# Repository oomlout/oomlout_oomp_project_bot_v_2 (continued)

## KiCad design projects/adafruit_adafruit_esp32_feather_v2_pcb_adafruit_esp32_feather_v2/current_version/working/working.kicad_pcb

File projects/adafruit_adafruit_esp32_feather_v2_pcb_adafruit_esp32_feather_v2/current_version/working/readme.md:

# adafruit_esp32_feather_v2_pcb
 
## summary 
* id: adafruit_adafruit_esp32_feather_v2_pcb_adafruit_esp32_feather_v2
* user: adafruit
* name: adafruit_esp32_feather_v2_pcb
* board: adafruit_esp32_feather_v2
* repo: https://github.com/adafruit/Adafruit-ESP32-Feather-V2-PCB

* src_file_repo_sch: 
* src_file_repo_sch_link: https://github.com/adafruit/Adafruit-ESP32-Feather-V2-PCB/tree/main/
* full details link: https://github.com/oomlout/oomlout_oomp_project_bot_v_2/tree/main/projects/adafruit_adafruit_esp32_feather_v2_pcb_adafruit_esp32_feather_v2/current_version/working  

## schematic  
  
[schematic (pdf)](working_schematic.pdf) 

## pcb  

[board (pdf)](working.pdf)  

## working_bom
| Id | Designator | Footprint | Quantity | Designation | Supplier and ref |  | None | 
| --- | --- | --- | --- | --- | --- | --- | --- | 
| 1 | LED1 | LED3535 | 1 | WS2812B3535 |  |  | [''] | 
| 2 | R9 | RESPACK_4X0603 | 1 | 47K |  |  | [''] | 
| 3 | D4 | SOD-123 | 1 | MBR540 |  |  | [''] | 
| 4 | R3,R1 | 0603-NO | 2 | 200K |  |  | [''] | 
| 5 | R4,R2,R5,R6,R10 | 0603-NO | 5 | 5.1K |  |  | [''] | 
| 6 | U$34,U$35 | FIDUCIAL_1MM | 2 | FIDUCIAL_1MM |  |  | [''] | 
| 7 | C1,C2,C13 | 0805-NO | 3 | 10uF |  |  | [''] | 
| 8 | JP1 | 1X16_ROUND | 1 |  |  |  | [''] | 
| 9 | U$31,U$32 | MOUNTINGHOLE_2.5_PLATED | 2 | MOUNTINGHOLE2.5 |  |  | [''] | 
| 10 | CHG0 | CHIPLED_0603_NOOUTLINE | 1 | ORANGE |  |  | [''] | 
| 11 | U2,U1 | SOT23-5 | 2 | AP2112-3.3 |  |  | [''] | 
| 12 | C8,C3,C7,C6 | 0805-NO | 4 | 10ÂµF |  |  | [''] | 
| 13 | C5,C4,C9,C10 | 0603-NO | 4 | 1uF |  |  | [''] | 
| 14 | Q5 | SOT363 | 1 | DUAL NPN |  |  | [''] | 
| 15 | @HOLE0,@HOLE1 |  | 2 |  |  |  | [''] | 
| 16 | U$14 | ADAFRUIT_2.5MM | 1 |  |  |  | [''] | 
| 17 | JP3 | 1X12_ROUND | 1 |  |  |  | [''] | 
| 18 | D3 | CHIPLED_0603_NOOUTLINE | 1 | RED |  |  | [''] | 
| 19 | U$15 | ADAFRUIT_3.5MM | 1 |  |  |  | [''] | 
| 20 | R7,R12 | 0603-NO | 2 | 100K |  |  | [''] | 
| 21 | CONN1 | JST_SH4_RA | 1 | STEMMA_I2C_QTRA |  |  | [''] | 
| 22 | X6 | USB_C_CUSB31-CFM2AX-01-X | 1 | USB Type C |  |  | [''] | 
| 23 | SW1,SW2 | BTN_KMR2_4.6X2.8 | 2 | KMR2 |  |  | [''] | 
| 24 | IC3 | QFN24_4MM_SMSC | 1 | CP2102N-24 |  |  | [''] | 
| 25 | Q3 | SOT23-R | 1 | DMG3415U |  |  | [''] | 
| 26 | R13 | RESPACK_4X0603 | 1 | 10K |  |  | [''] | 
| 27 | C12,C11 | 0603-NO | 2 | 0.1uF |  |  | [''] | 
| 28 | X3 | ESP32-PICO-MINI | 1 | ESP32-PICO-MINI-02MINI |  |  | [''] | 
| 29 | U3 | SOT23-5 | 1 | MCP73831T-2ACI/OT |  |  | [''] | 
| 30 | X1 | JSTPH2_BATT | 1 | JSTPH |  |  | [''] | 
| 31 | D+1,D-1 | B1,27 | 2 | TPB1,27 |  |  | [''] | 
| 32 | U$43 | HUZZAH32 | 1 |  |  |  | [''] | 
| 33 | U$7 | ADAFRUIT_5MM | 1 |  |  |  | [''] | 
| 34 | U$13 | PCBFEAT-REV-040 | 1 |  |  |  | [''] | 
| 35 | U$9 | FEATHERLOGO_MED | 1 |  |  |  | [''] | 

## bom_schematic
| Ref | Qnty | Value | Cmp name | Footprint | Description | Vendor | DNP | 
| --- | --- | --- | --- | --- | --- | --- | --- | 
| C1, C2, C13 | 3 | 10uF | CAP_CERAMIC0805-NOOUTLINE | working:0805-NO |  |  |  | 
| C3, C6, C7, C8 | 4 | 10ÂµF | CAP_CERAMIC0805-NOOUTLINE | working:0805-NO |  |  |  | 
| C4, C5, C9, C10 | 4 | 1uF | CAP_CERAMIC0603_NO | working:0603-NO |  |  |  | 
| C11, C12 | 2 | 0.1uF | CAP_CERAMIC0603_NO | working:0603-NO |  |  |  | 
| CHG0 | 1 | ORANGE | LED0603_NOOUTLINE | working:CHIPLED_0603_NOOUTLINE |  |  |  | 
| CONN1 | 1 | STEMMA_I2C_QTRA | STEMMA_I2C_QTRA | working:JST_SH4_RA |  |  |  | 
| D3 | 1 | RED | LED0603_NOOUTLINE | working:CHIPLED_0603_NOOUTLINE |  |  |  | 
| D4 | 1 | MBR540 | DIODE-SCHOTTKYSOD-123 | working:SOD-123 |  |  |  | 
| D+1 | 1 | TPB1,27 | TPB1,27 | working:B1,27 |  |  |  | 
| D-1 | 1 | TPB1,27 | TPB1,27 | working:B1,27 |  |  |  | 
| IC3 | 1 | CP2102N-24 | CP2102N-24 | working:QFN24_4MM_SMSC |  |  |  | 
| JP1 | 1 | HEADER-1X16ROUND | HEADER-1X16ROUND | working:1X16_ROUND |  |  |  | 
| JP3 | 1 | HEADER-1X12 | HEADER-1X12 | working:1X12_ROUND |  |  |  | 
| LED1 | 1 | WS2812B3535 | WS2812B3535 | working:LED3535 |  |  |  | 
| Q3 | 1 | DMG3415U | MOSFET-P | working:SOT23-R |  |  |  | 
| Q5 | 1 | DUAL NPN | MOSFET-N_DUAL | working:SOT363 |  |  |  | 
| R1, R3 | 2 | 200K | RESISTOR_0603_NOOUT | working:0603-NO |  |  |  | 
| R2, R4, R5, R6, R10 | 5 | 5.1K | RESISTOR_0603_NOOUT | working:0603-NO |  |  |  | 
| R7, R12 | 2 | 100K | RESISTOR_0603_NOOUT | working:0603-NO |  |  |  | 
| R9 | 1 | 47K | RESISTOR_4PACK | working:RESPACK_4X0603 |  |  |  | 
| R13 | 1 | 10K | RESISTOR_4PACK | working:RESPACK_4X0603 |  |  |  | 
| SW1, SW2 | 2 | KMR2 | SWITCH_TACT_SMT4.6X2.8 | working:BTN_KMR2_4.6X2.8 |  |  |  | 
| U1, U2 | 2 | AP2112-3.3 | VREG_SOT23-5 | working:SOT23-5 |  |  |  | 
| U3 | 1 | MCP73831T-2ACI/OT | MCP73831/2 | working:SOT23-5 |  |  |  | 
| U$31, U$32 | 2 | MOUNTINGHOLE2.5 | MOUNTINGHOLE2.5 | working:MOUNTINGHOLE_2.5_PLATED |  |  |  | 
| U$34, U$35 | 2 | FIDUCIAL_1MM | FIDUCIAL_1MM | working:FIDUCIAL_1MM |  |  |  | 
| X1 | 1 | CON_JST_PH_2PIN_MT_BATT | CON_JST_PH_2PIN_MT_BATT | working:JSTPH2_BATT |  |  |  | 
| X3 | 1 | ESP32-PICO-MINI-02MINI | ESP32-PICO-MINI-02MINI | working:ESP32-PICO-MINI |  |  |  | 
| X6 | 1 | USB Type C | USB_C | working:USB_C_CUSB31-CFM2AX-01-X |  |  |  | 

## mounting_holes
| x | y | package | value | ref | size | 
| --- | --- | --- | --- | --- | --- | 
| 0.0 | 17.78 | MOUNTINGHOLE_2.5_PLATED | MOUNTINGHOLE2.5 | U$31 | m3 | 
| 0.0 | 0.0 | MOUNTINGHOLE_2.5_PLATED | MOUNTINGHOLE2.5 | U$32 | m3 |

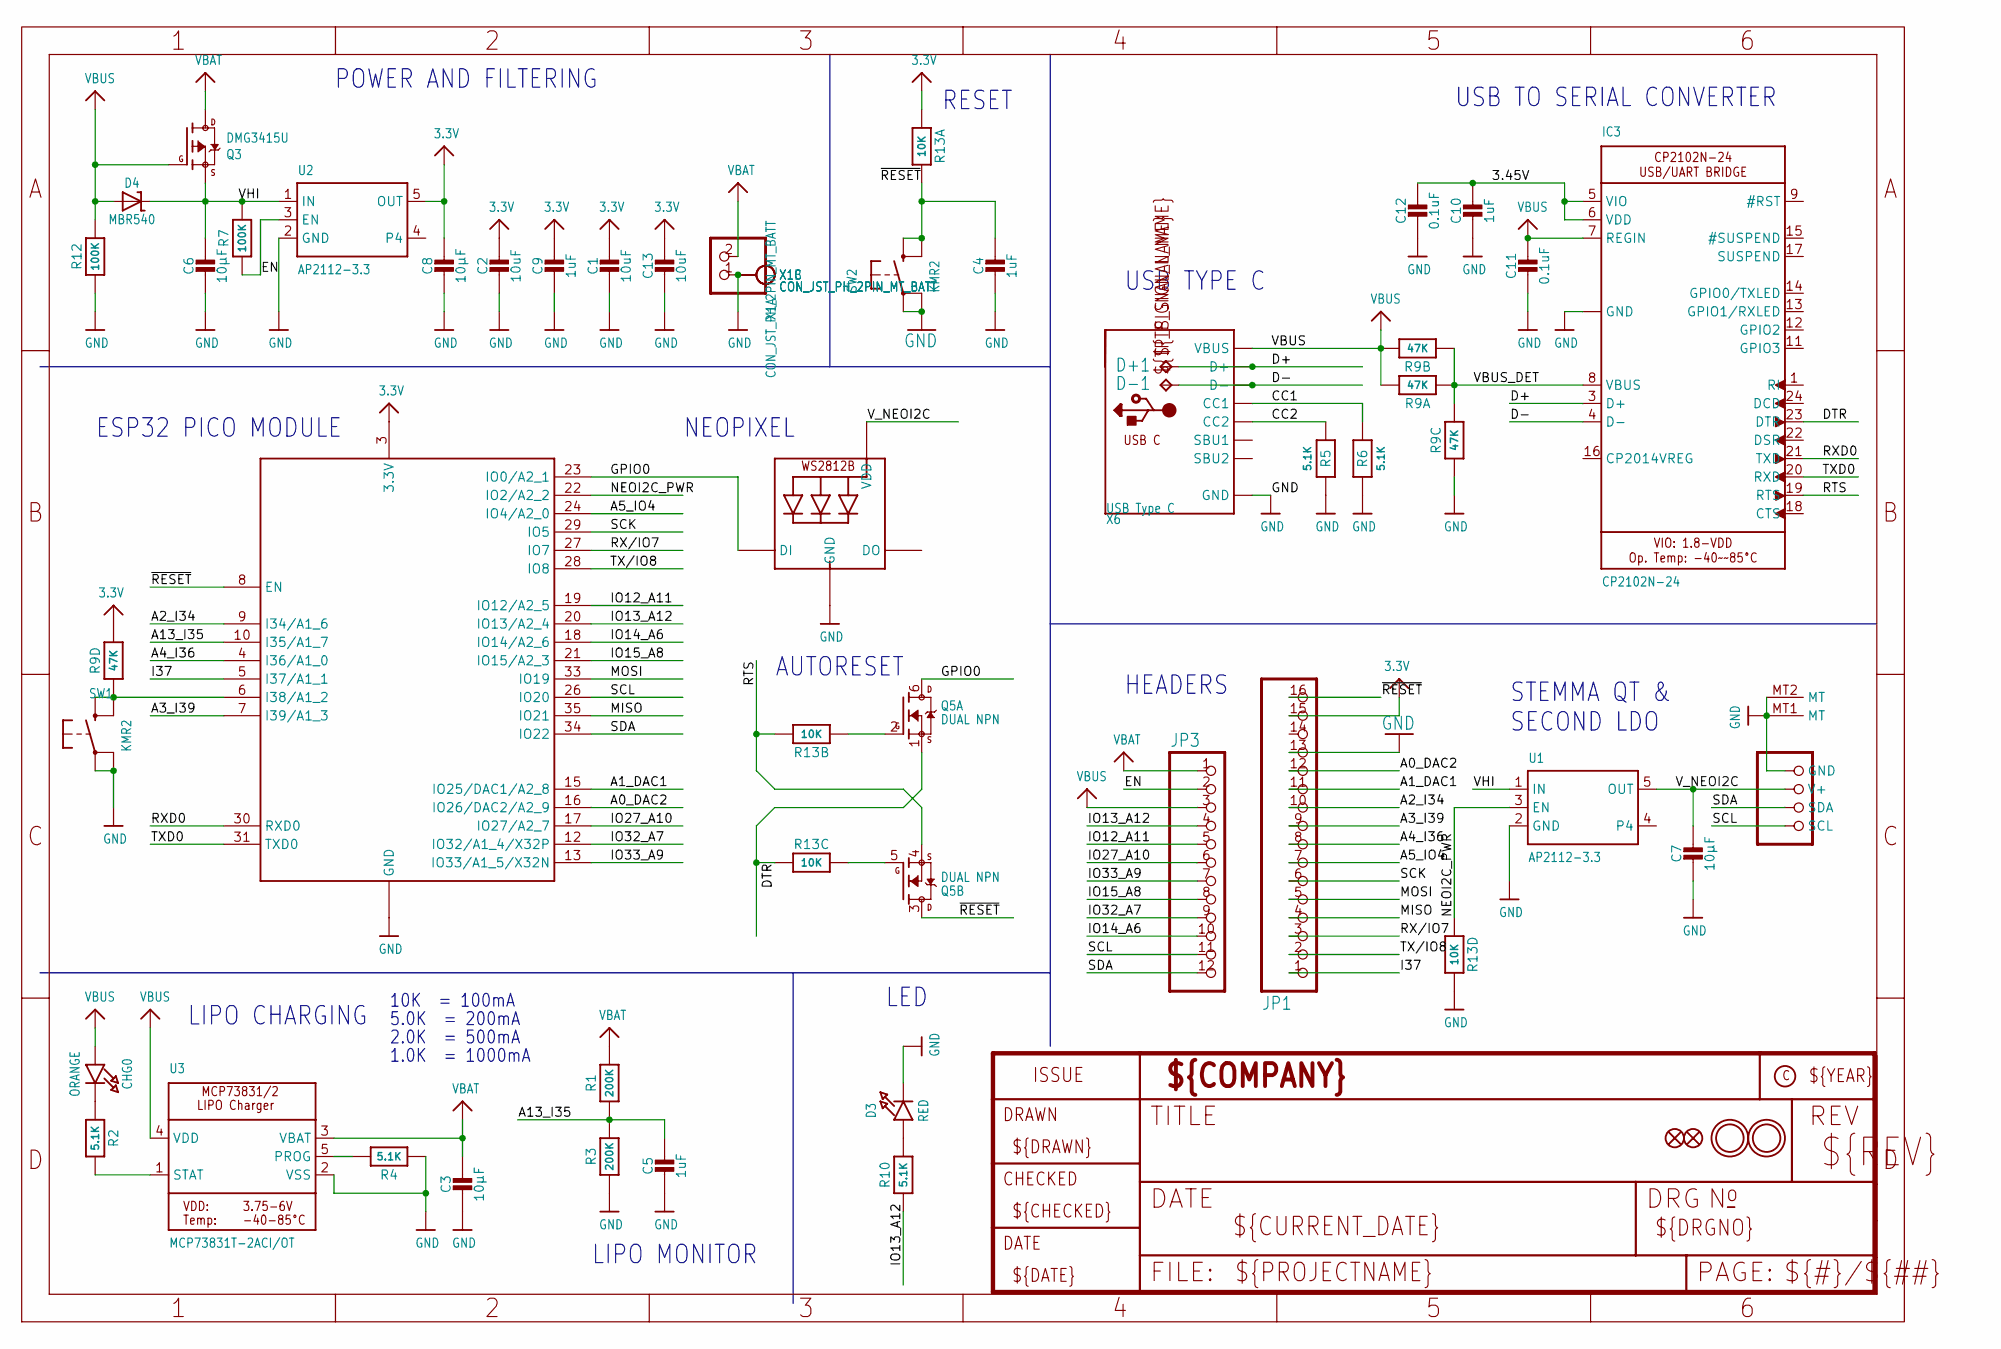
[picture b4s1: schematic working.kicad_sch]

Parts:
C1, C2, C13: 10uF; 0805-NO
C3, C6, C7, C8: 10µF; 0805-NO
C4, C5, C9, C10: 1uF; 0603-NO
C11, C12: 0.1uF; 0603-NO
CHG0: ORANGE; CHIPLED_0603_NOOUTLINE
CONN1: STEMMA_I2C_QTRA; JST_SH4_RA
D3: RED; CHIPLED_0603_NOOUTLINE
D4: MBR540; SOD-123
D+1: TPB1,27; B1,27
D-1: TPB1,27; B1,27
IC3: CP2102N-24; QFN24_4MM_SMSC
JP1: HEADER-1X16ROUND; 1X16_ROUND
JP3: HEADER-1X12; 1X12_ROUND
LED1: WS2812B3535; LED3535
Q3: DMG3415U; SOT23-R
Q5: DUAL NPN; SOT363
R1, R3: 200K; 0603-NO
R2, R4, R5, R6, R10: 5.1K; 0603-NO
R7, R12: 100K; 0603-NO
R9: 47K; RESPACK_4X0603
R13: 10K; RESPACK_4X0603
SW1, SW2: KMR2; BTN_KMR2_4.6X2.8
U1, U2: AP2112-3.3; SOT23-5
U3: MCP73831T-2ACI/OT; SOT23-5
U$31, U$32: MOUNTINGHOLE2.5; MOUNTINGHOLE_2.5_PLATED
U$34, U$35: FIDUCIAL_1MM
X1: CON_JST_PH_2PIN_MT_BATT; JSTPH2_BATT
X3: ESP32-PICO-MINI-02MINI; ESP32-PICO-MINI
X6: USB Type C; USB_C_CUSB31-CFM2AX-01-X

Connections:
3.3V: C1.1, C2.1, C8.1, C9.1, C13.1, JP1.15, R9.5 (2), R13.1, U2.5 (OUT), X3.3 (3.3V)
3.45V: C10.1, C12.1, IC3.5 (VIO), IC3.6 (VDD)
A0_DAC2: JP1.12, X3.16 (IO26/DAC2/A2_9)
A1_DAC1: JP1.11, X3.15 (IO25/DAC1/A2_8)
A2_I34: JP1.10, X3.9 (I34/A1_6)
A3_I39: JP1.9, X3.7 (I39/A1_3)
A4_I36: JP1.8, X3.4 (I36/A1_0)
A5_IO4: JP1.7, X3.24 (IO4/A2_0)
A13_I35: C5.1, R1.1, R3.2, X3.10 (I35/A1_7)
CC1: R6.2, X6.A5 (CC1)
CC2: R5.2, X6.B5 (CC2)
D+: D+1.TP, IC3.3 (D+), X6.A6 (D+), X6.B6 (D+)
D-: D-1.TP, IC3.4 (D-), X6.A7 (D-), X6.B7 (D-)
DTR: IC3.23 (DTR), Q5.1 (S), R13.3 (1)
EN: JP3.2, R7.1, U2.3 (EN)
GND: C1.2, C2.2, C3.2, C4.2, C5.2, C6.2, C7.2, C8.2, C9.2, C10.2, C11.2, C12.2, C13.2, CONN1.1 (GND), CONN1.MT1 (MT), CONN1.MT2 (MT), D3.C, IC3.2 (GND), IC3.THERM (GND), JP1.13, LED1.4 (GND), R3.1, R4.1, R5.1, R6.1, R9.3 (1), R12.1, R13.5 (2), SW1.A, SW1.A' (P1), SW2.A, SW2.A' (P1), U1.2 (GND), U2.2 (GND), U3.2 (VSS), X1.1, X1.NC1, X1.NC2, X3.1 (GND), X3.2 (GND), X3.11 (GND), X3.14 (GND), X3.36 (GND), X3.37 (GND), X3.38 (GND), X3.39 (GND), X3.40 (GND), X3.41 (GND), X3.42 (GND), X3.43 (GND), X3.44 (GND), X3.45 (GND), X3.46 (GND), X3.47 (GND), X3.48 (GND), X3.49 (GND), X3.50 (GND), X3.51 (GND), X3.52 (GND), X3.53 (GND), X3.54 (GND), X3.55 (GND), X3.56 (GND), X3.57 (GND), X3.58 (GND), X3.59 (GND), X3.60 (GND), X3.61 (GND), X6.A1B12 (GND), X6.B1A12 (GND)
GPIO0: LED1.1 (DI), Q5.6 (D), X3.23 (IO0/A2_1)
I37: JP1.1, X3.5 (I37/A1_1)
IO12_A11: JP3.5, X3.19 (IO12/A2_5)
IO13_A12: JP3.4, R10.1, X3.20 (IO13/A2_4)
IO14_A6: JP3.10, X3.18 (IO14/A2_6)
IO15_A8: JP3.8, X3.21 (IO15/A2_3)
IO27_A10: JP3.6, X3.17 (IO27/A2_7)
IO32_A7: JP3.9, X3.12 (IO32/A1_4/X32P)
IO33_A9: JP3.7, X3.13 (IO33/A1_5/X32N)
MISO: JP1.4, X3.35 (IO21)
MOSI: JP1.5, X3.33 (IO19)
unnamed: CHG0.C, R2.1
unnamed: R2.2, U3.1 (STAT)
unnamed: R4.2, U3.5 (PROG)
unnamed: D3.A, R10.2
unnamed: R9.4 (1), SW1.B (S), SW1.B' (S1), X3.6 (I38/A1_2)
unnamed: Q5.5 (G), R13.6 (2)
unnamed: Q5.2 (G), R13.2 (1)
NEOI2C_PWR: R13.4 (1), U1.3 (EN), X3.22 (IO2/A2_2)
RTS: IC3.19 (RTS), Q5.4 (S), R13.7 (2)
RX/IO7: JP1.3, X3.27 (IO7)
RXD0: IC3.21 (TXD), X3.30 (RXD0)
SCK: JP1.6, X3.29 (IO5)
SCL: CONN1.4 (SCL), JP3.11, X3.26 (IO20)
SDA: CONN1.3 (SDA), JP3.12, X3.34 (IO22)
TX/IO8: JP1.2, X3.28 (IO8)
TXD0: IC3.20 (RXD), X3.31 (TXD0)
VBAT: C3.1, JP3.1, Q3.3 (D), R1.2, U3.3 (VBAT), X1.2
VBUS: C11.1, CHG0.A, D4.A, IC3.7 (REGIN), JP3.3, Q3.1 (G), R9.7 (2), R9.8 (2), R12.2, U3.4 (VDD), X6.A4B9 (VBUS), X6.B4A9 (VBUS)
VBUS_DET: IC3.8 (VBUS), R9.1, R9.2 (1), R9.6 (2)
VHI: C6.1, D4.C, Q3.2 (S), R7.2, U1.1 (IN), U2.1 (IN)
V_NEOI2C: C7.1, CONN1.2 (V+), LED1.2 (VDD), U1.5 (OUT)
~RESET: C4.1, JP1.16, Q5.3 (D), R13.8 (2), SW2.B (S), SW2.B' (S1), X3.8 (EN)

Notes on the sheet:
LIPO CHARGING
HEADERS
RESET
ESP32 PICO MODULE
2.0K = 500mA
USB TO SERIAL CONVERTER
AUTORESET
LED
10K = 100mA
LIPO MONITOR
NEOPIXEL
1.0K = 1000mA
STEMMA QT & SECOND LDO
POWER AND FILTERING
USB TYPE C
5.0K = 200mA

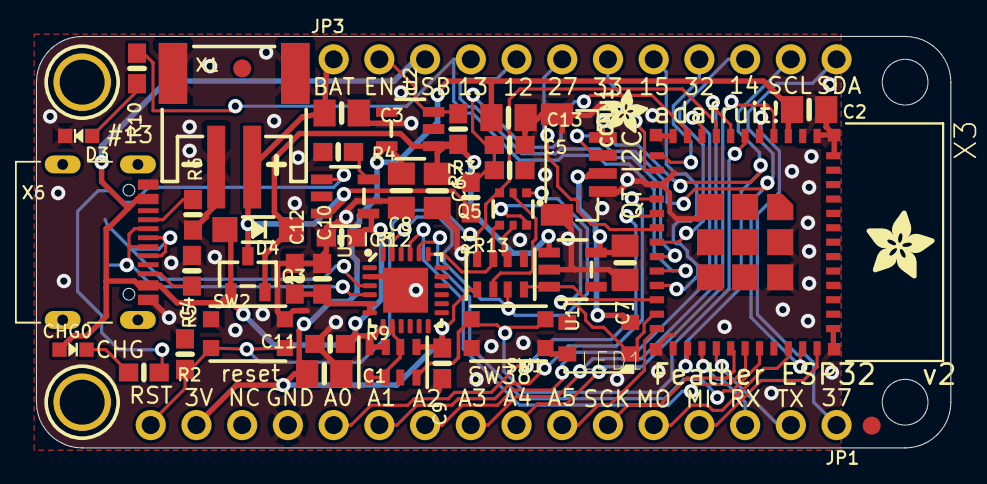
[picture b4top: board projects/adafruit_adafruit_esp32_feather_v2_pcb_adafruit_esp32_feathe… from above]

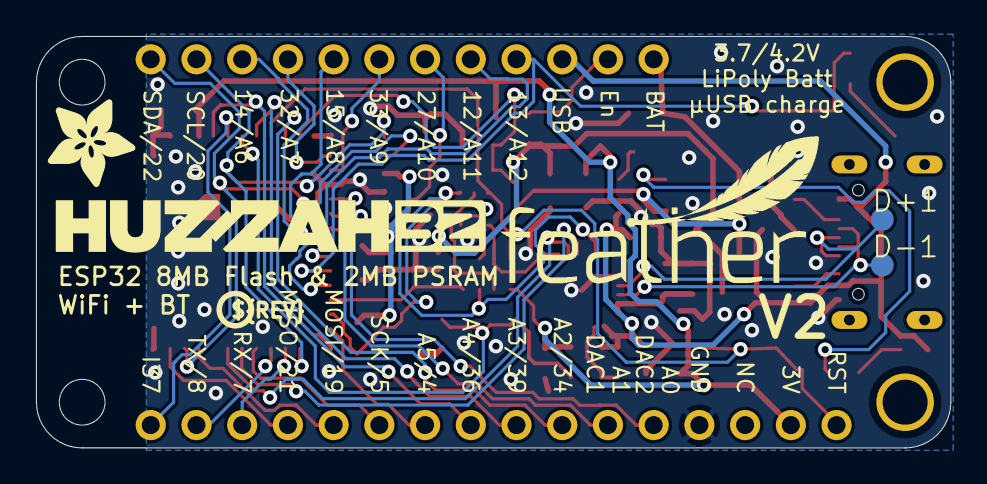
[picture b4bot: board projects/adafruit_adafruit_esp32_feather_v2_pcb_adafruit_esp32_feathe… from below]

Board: 2 copper layers, 50.8 x 22.9 mm, 56 parts (6 on the bottom side), 49 nets.

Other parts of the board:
@HOLE0, @HOLE1: (no value)
U$7: ADAFRUIT_5MM
U$9: FEATHERLOGO_MED
U$13: PCBFEAT-REV-040
U$14: ADAFRUIT_2.5MM
U$15: ADAFRUIT_3.5MM
U$43: HUZZAH32

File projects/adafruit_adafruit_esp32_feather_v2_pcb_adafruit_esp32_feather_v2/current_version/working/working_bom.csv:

"Id";"Designator";"Footprint";"Quantity";"Designation";"Supplier and ref";
1;"LED1";"LED3535";1;"WS2812B3535";;;
2;"R9";"RESPACK_4X0603";1;"47K";;;
3;"D4";"SOD-123";1;"MBR540";;;
4;"R3,R1";"0603-NO";2;"200K";;;
5;"R4,R2,R5,R6,R10";"0603-NO";5;"5.1K";;;
6;"U$34,U$35";"FIDUCIAL_1MM";2;"FIDUCIAL_1MM";;;
7;"C1,C2,C13";"0805-NO";3;"10uF";;;
8;"JP1";"1X16_ROUND";1;"";;;
9;"U$31,U$32";"MOUNTINGHOLE_2.5_PLATED";2;"MOUNTINGHOLE2.5";;;
10;"CHG0";"CHIPLED_0603_NOOUTLINE";1;"ORANGE";;;
11;"U2,U1";"SOT23-5";2;"AP2112-3.3";;;
12;"C8,C3,C7,C6";"0805-NO";4;"10µF";;;
13;"C5,C4,C9,C10";"0603-NO";4;"1uF";;;
14;"Q5";"SOT363";1;"DUAL NPN";;;
15;"@HOLE0,@HOLE1";"";2;"";;;
16;"U$14";"ADAFRUIT_2.5MM";1;"";;;
17;"JP3";"1X12_ROUND";1;"";;;
18;"D3";"CHIPLED_0603_NOOUTLINE";1;"RED";;;
19;"U$15";"ADAFRUIT_3.5MM";1;"";;;
20;"R7,R12";"0603-NO";2;"100K";;;
21;"CONN1";"JST_SH4_RA";1;"STEMMA_I2C_QTRA";;;
22;"X6";"USB_C_CUSB31-CFM2AX-01-X";1;"USB Type C";;;
23;"SW1,SW2";"BTN_KMR2_4.6X2.8";2;"KMR2";;;
24;"IC3";"QFN24_4MM_SMSC";1;"CP2102N-24";;;
25;"Q3";"SOT23-R";1;"DMG3415U";;;
26;"R13";"RESPACK_4X0603";1;"10K";;;
27;"C12,C11";"0603-NO";2;"0.1uF";;;
28;"X3";"ESP32-PICO-MINI";1;"ESP32-PICO-MINI-02MINI";;;
29;"U3";"SOT23-5";1;"MCP73831T-2ACI/OT";;;
30;"X1";"JSTPH2_BATT";1;"JSTPH";;;
31;"D+1,D-1";"B1,27";2;"TPB1,27";;;
32;"U$43";"HUZZAH32";1;"";;;
33;"U$7";"ADAFRUIT_5MM";1;"";;;
34;"U$13";"PCBFEAT-REV-040";1;"";;;
35;"U$9";"FEATHERLOGO_MED";1;"";;;

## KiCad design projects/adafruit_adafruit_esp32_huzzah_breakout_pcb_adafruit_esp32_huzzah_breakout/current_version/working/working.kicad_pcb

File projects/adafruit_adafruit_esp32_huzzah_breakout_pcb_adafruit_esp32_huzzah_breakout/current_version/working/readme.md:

# adafruit_esp32_huzzah_breakout_pcb
 
## summary 
* id: adafruit_adafruit_esp32_huzzah_breakout_pcb_adafruit_esp32_huzzah_breakout
* user: adafruit
* name: adafruit_esp32_huzzah_breakout_pcb
* board: adafruit_esp32_huzzah_breakout
* repo: https://github.com/adafruit/Adafruit-ESP32-HUZZAH-Breakout-PCB

* src_file_repo_sch: 
* src_file_repo_sch_link: https://github.com/adafruit/Adafruit-ESP32-HUZZAH-Breakout-PCB/tree/master/
* full details link: https://github.com/oomlout/oomlout_oomp_project_bot_v_2/tree/main/projects/adafruit_adafruit_esp32_huzzah_breakout_pcb_adafruit_esp32_huzzah_breakout/current_version/working  

## schematic  
  
[schematic (pdf)](working_schematic.pdf) 

## pcb  

[board (pdf)](working.pdf)  

## working_bom
| Id | Designator | Footprint | Quantity | Designation | Supplier and ref |  | None | 
| --- | --- | --- | --- | --- | --- | --- | --- | 
| 1 | U$3 | ADAFRUIT_2.5MM | 1 |  |  |  | [''] | 
| 2 | C2,C1,C4,C3 | 0805-NO | 4 | 10uF |  |  | [''] | 
| 3 | FID1,FID3 | FIDUCIAL_1MM | 2 | FIDUCIAL_1MM |  |  | [''] | 
| 4 | D6,D5 | SOD-123 | 2 | MBR120 |  |  | [''] | 
| 5 | JP1 | 1X06_ROUND_70 | 1 | FTDI |  |  | [''] | 
| 6 | U$15,U$16 | MOUNTINGHOLE_2.5_PLATED | 2 | MOUNTINGHOLE2.5 |  |  | [''] | 
| 7 | JP2,JP5 | 1X15_ROUND_70 | 2 |  |  |  | [''] | 
| 8 | D1,D2 | SOD-323 | 2 | 1n4148 |  |  | [''] | 
| 9 | C5 | 0805-NO | 1 | 1uF |  |  | [''] | 
| 10 | R2 | 0603-NO | 1 | 1K |  |  | [''] | 
| 11 | SW2,SW1 | BTN_KMR2_4.6X2.8 | 2 | KMR2 |  |  | [''] | 
| 12 | D3 | CHIPLED_0805_NOOUTLINE | 1 | RED |  |  | [''] | 
| 13 | R4 | 0603-NO | 1 | 10K |  |  | [''] | 
| 14 | U1 | SOT23-5 | 1 | AP2112-3.3 |  |  | [''] | 
| 15 | X1 | WROOM32 | 1 | ESP32_WROOM32 |  |  | [''] | 
| 16 | U$12 | ADAFRUIT_TEXT_20MM | 1 |  |  |  | [''] | 
| 17 | U$2 | HUZZAHLOGO | 1 |  |  |  | [''] | 
| 18 | X2 | JSTPH2 | 1 | JSTPH |  |  | [''] | 
| 19 | U$13 | PCBFEAT-REV-040 | 1 |  |  |  | [''] | 

## bom_schematic
| Ref | Qnty | Value | Cmp name | Footprint | Description | Vendor | DNP | 
| --- | --- | --- | --- | --- | --- | --- | --- | 
| C1, C2, C3, C4 | 4 | 10uF | CAP_CERAMIC0805-NOOUTLINE | working:0805-NO |  |  |  | 
| C5 | 1 | 1uF | CAP_CERAMIC0805-NOOUTLINE | working:0805-NO |  |  |  | 
| D1, D2 | 2 | 1n4148 | DIODESOD-323 | working:SOD-323 |  |  |  | 
| D3 | 1 | RED | LED0805_NOOUTLINE | working:CHIPLED_0805_NOOUTLINE |  |  |  | 
| D5, D6 | 2 | MBR120 | DIODE-SCHOTTKYSOD-123 | working:SOD-123 |  |  |  | 
| FID1, FID3 | 2 | FIDUCIAL_1MM | FIDUCIAL_1MM | working:FIDUCIAL_1MM |  |  |  | 
| JP1 | 1 | FTDI | HEADER-1X670MIL | working:1X06_ROUND_70 |  |  |  | 
| JP2, JP5 | 2 | HEADER-1X15 | HEADER-1X15 | working:1X15_ROUND_70 |  |  |  | 
| R2 | 1 | 1K | RESISTOR_0603_NOOUT | working:0603-NO |  |  |  | 
| R4 | 1 | 10K | RESISTOR_0603_NOOUT | working:0603-NO |  |  |  | 
| SW1, SW2 | 2 | KMR2 | SWITCH_TACT_SMT4.6X2.8 | working:BTN_KMR2_4.6X2.8 |  |  |  | 
| U1 | 1 | AP2112-3.3 | VREG_SOT23-5 | working:SOT23-5 |  |  |  | 
| U$15, U$16 | 2 | MOUNTINGHOLE2.5 | MOUNTINGHOLE2.5 | working:MOUNTINGHOLE_2.5_PLATED |  |  |  | 
| X1 | 1 | ESP32_WROOM32 | ESP32_WROOM32 | working:WROOM32 |  |  |  | 
| X2 | 1 | JSTPH | CON_JST_PH_2PIN | working:JSTPH2 |  |  |  | 

## mounting_holes
| x | y | package | value | ref | size | 
| --- | --- | --- | --- | --- | --- | 
| 0.0 | 0.0 | MOUNTINGHOLE_2.5_PLATED | MOUNTINGHOLE2.5 | U$15 | m3 | 
| 20.32 | 0.0 | MOUNTINGHOLE_2.5_PLATED | MOUNTINGHOLE2.5 | U$16 | m3 |

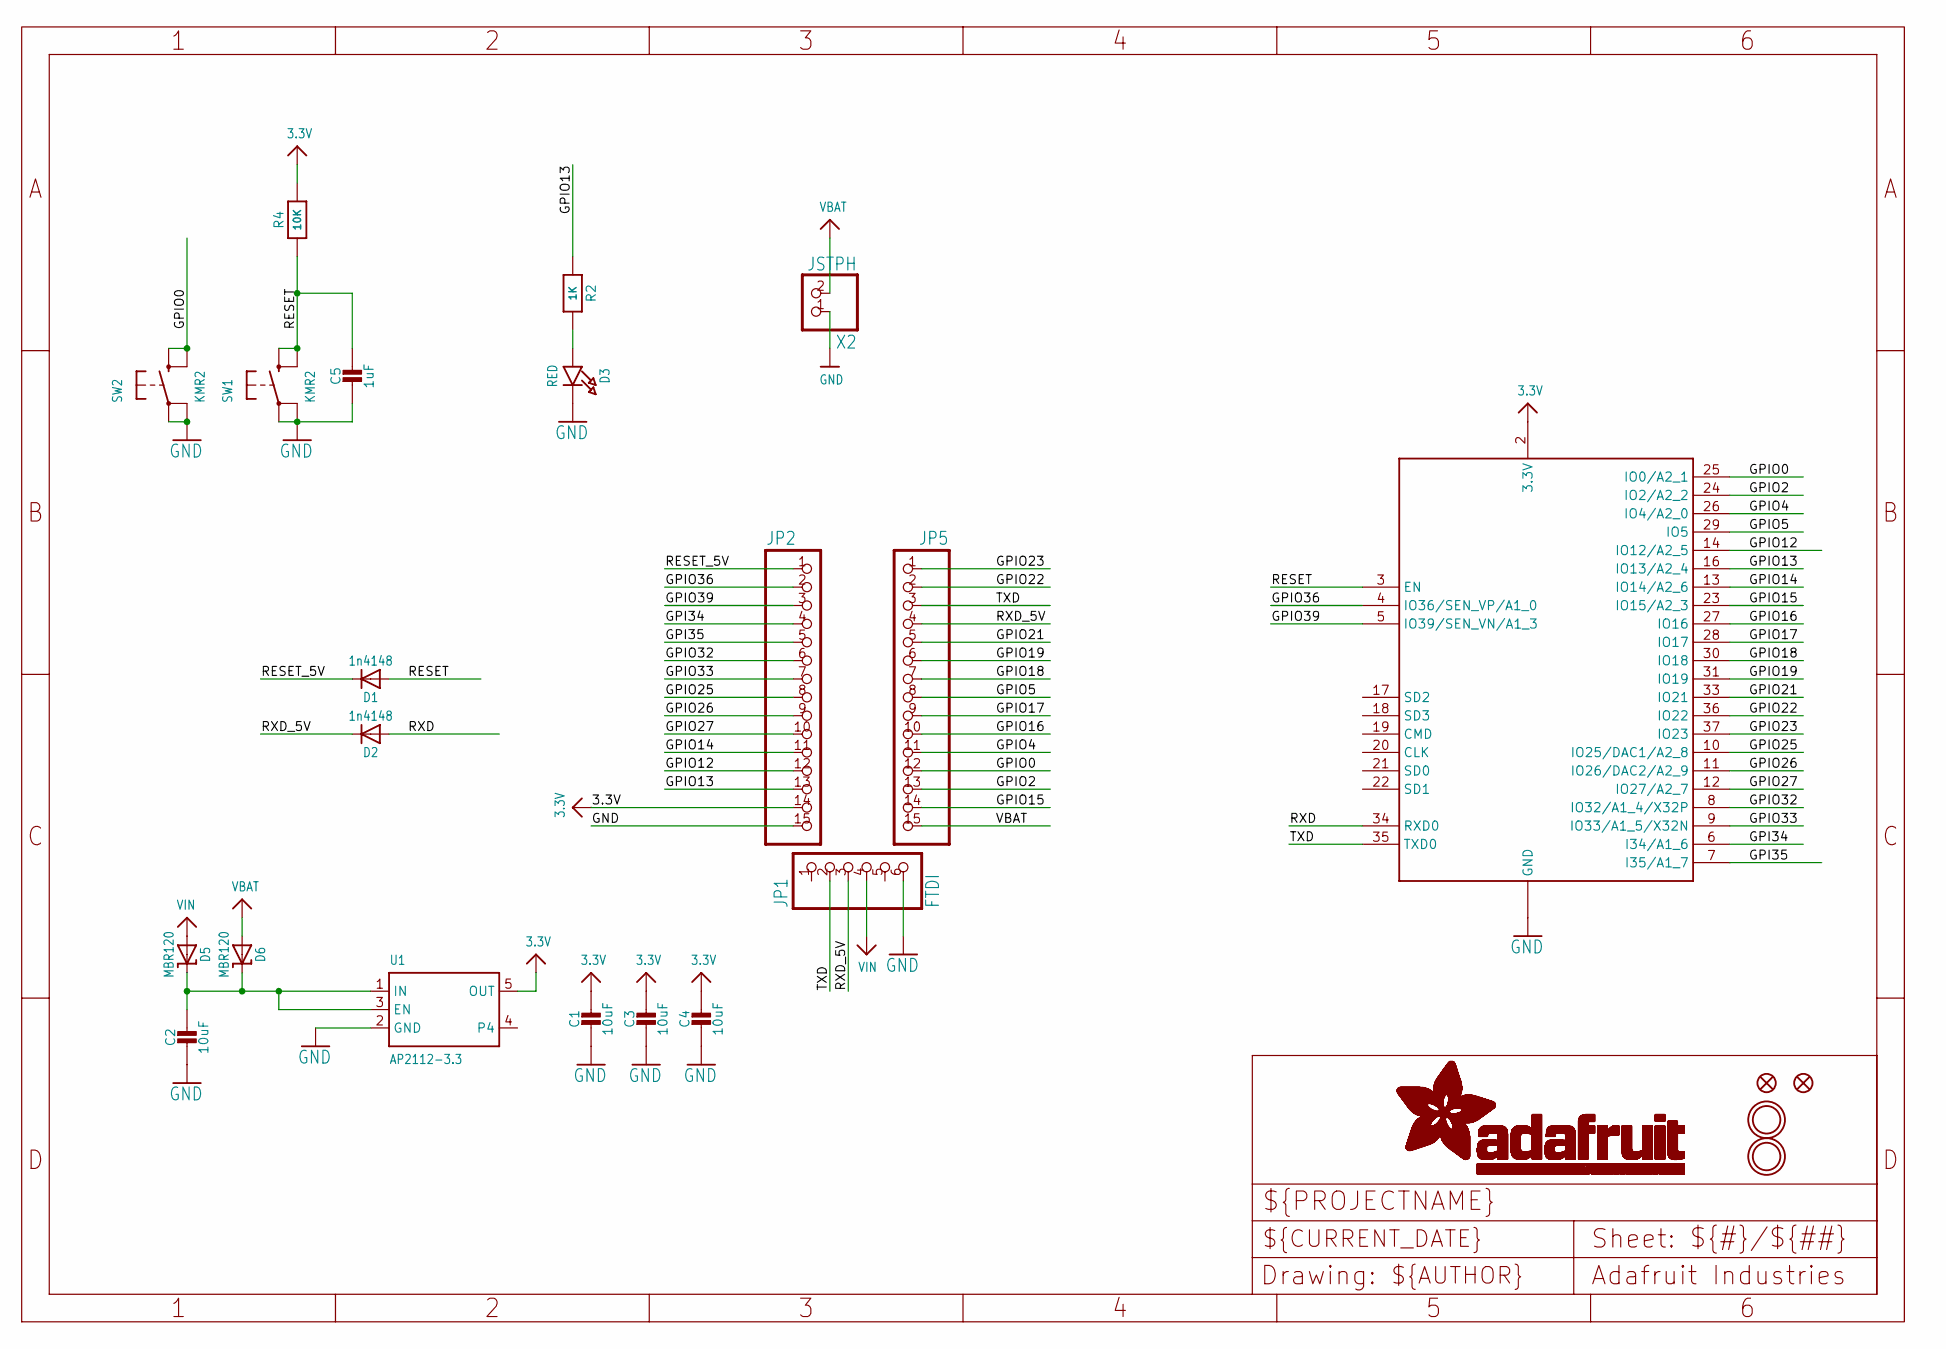
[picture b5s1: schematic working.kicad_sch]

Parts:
C1, C2, C3, C4: 10uF; 0805-NO
C5: 1uF; 0805-NO
D1, D2: 1n4148; SOD-323
D3: RED; CHIPLED_0805_NOOUTLINE
D5, D6: MBR120; SOD-123
FID1, FID3: FIDUCIAL_1MM
JP1: FTDI; 1X06_ROUND_70
JP2, JP5: HEADER-1X15; 1X15_ROUND_70
R2: 1K; 0603-NO
R4: 10K; 0603-NO
SW1, SW2: KMR2; BTN_KMR2_4.6X2.8
U1: AP2112-3.3; SOT23-5
U$15, U$16: MOUNTINGHOLE2.5; MOUNTINGHOLE_2.5_PLATED
X1: ESP32_WROOM32; WROOM32
X2: JSTPH; JSTPH2

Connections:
3.3V: C1.1, C3.1, C4.1, JP2.14, R4.2, U1.5 (OUT), X1.2 (3.3V)
GND: C1.2, C2.2, C3.2, C4.2, C5.2, D3.C, JP1.6, JP2.15, SW1.A, SW1.A' (P1), SW2.A, SW2.A' (P1), U1.2 (GND), X1.1 (GND), X1.15 (GND), X1.38 (GND), X1.P$1 (GND), X2.1
GPI34: JP2.4, X1.6 (I34/A1_6)
GPI35: JP2.5, X1.7 (I35/A1_7)
GPIO0: JP5.12, SW2.B (S), SW2.B' (S1), X1.25 (IO0/A2_1)
GPIO2: JP5.13, X1.24 (IO2/A2_2)
GPIO4: JP5.11, X1.26 (IO4/A2_0)
GPIO5: JP5.8, X1.29 (IO5)
GPIO12: JP2.12, X1.14 (IO12/A2_5)
GPIO13: JP2.13, R2.1, X1.16 (IO13/A2_4)
GPIO14: JP2.11, X1.13 (IO14/A2_6)
GPIO15: JP5.14, X1.23 (IO15/A2_3)
GPIO16: JP5.10, X1.27 (IO16)
GPIO17: JP5.9, X1.28 (IO17)
GPIO18: JP5.7, X1.30 (IO18)
GPIO19: JP5.6, X1.31 (IO19)
GPIO21: JP5.5, X1.33 (IO21)
GPIO22: JP5.2, X1.36 (IO22)
GPIO23: JP5.1, X1.37 (IO23)
GPIO25: JP2.8, X1.10 (IO25/DAC1/A2_8)
GPIO26: JP2.9, X1.11 (IO26/DAC2/A2_9)
GPIO27: JP2.10, X1.12 (IO27/A2_7)
GPIO32: JP2.6, X1.8 (IO32/A1_4/X32P)
GPIO33: JP2.7, X1.9 (IO33/A1_5/X32N)
GPIO36: JP2.2, X1.4 (IO36/SEN_VP/A1_0)
GPIO39: JP2.3, X1.5 (IO39/SEN_VN/A1_3)
LDO_EN: C2.1, D5.C, D6.C, U1.1 (IN), U1.3 (EN)
unnamed: D3.A, R2.2
RESET: C5.1, D1.A, R4.1, SW1.B (S), SW1.B' (S1), X1.3 (EN)
RESET_5V: D1.C, JP2.1
RXD: D2.A, X1.34 (RXD0)
RXD_5V: D2.C, JP1.3, JP5.4
TXD: JP1.2, JP5.3, X1.35 (TXD0)
VBAT: D6.A, JP5.15, X2.2
VIN: D5.A, JP1.4

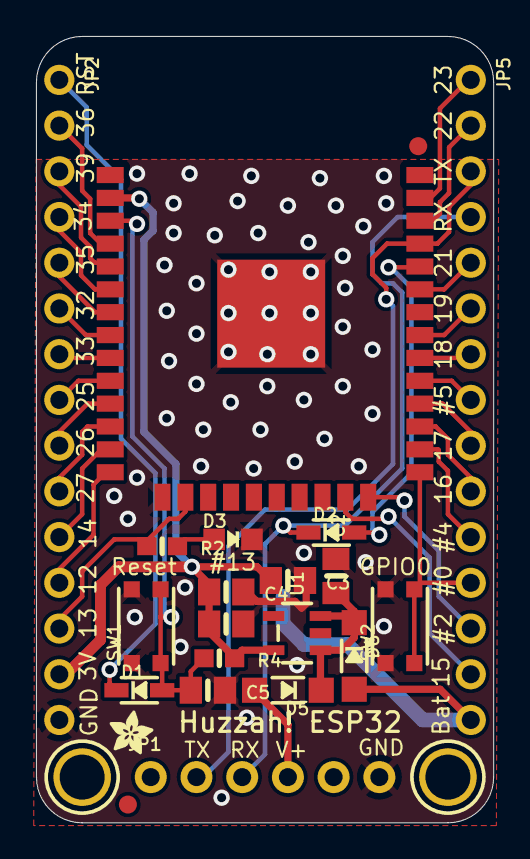
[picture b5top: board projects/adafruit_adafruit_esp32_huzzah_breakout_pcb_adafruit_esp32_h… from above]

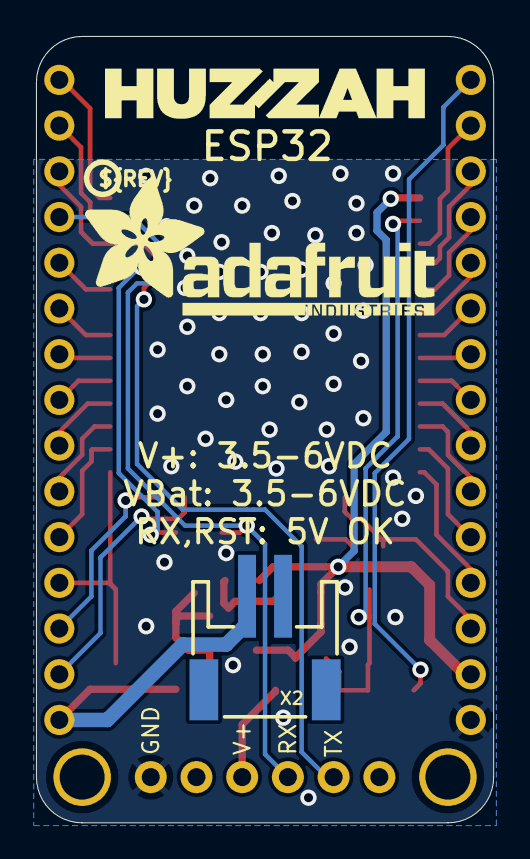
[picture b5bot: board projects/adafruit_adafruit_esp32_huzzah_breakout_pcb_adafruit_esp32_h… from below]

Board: 16 copper layers, 25.4 x 43.7 mm, 28 parts (4 on the bottom side), 35 nets.

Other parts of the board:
U$2: HUZZAHLOGO
U$3: ADAFRUIT_2.5MM
U$12: ADAFRUIT_TEXT_20MM
U$13: PCBFEAT-REV-040

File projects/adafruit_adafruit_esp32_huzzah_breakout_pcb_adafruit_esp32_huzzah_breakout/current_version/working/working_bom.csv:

"Id";"Designator";"Footprint";"Quantity";"Designation";"Supplier and ref";
1;"U$3";"ADAFRUIT_2.5MM";1;"";;;
2;"C2,C1,C4,C3";"0805-NO";4;"10uF";;;
3;"FID1,FID3";"FIDUCIAL_1MM";2;"FIDUCIAL_1MM";;;
4;"D6,D5";"SOD-123";2;"MBR120";;;
5;"JP1";"1X06_ROUND_70";1;"FTDI";;;
6;"U$15,U$16";"MOUNTINGHOLE_2.5_PLATED";2;"MOUNTINGHOLE2.5";;;
7;"JP2,JP5";"1X15_ROUND_70";2;"";;;
8;"D1,D2";"SOD-323";2;"1n4148";;;
9;"C5";"0805-NO";1;"1uF";;;
10;"R2";"0603-NO";1;"1K";;;
11;"SW2,SW1";"BTN_KMR2_4.6X2.8";2;"KMR2";;;
12;"D3";"CHIPLED_0805_NOOUTLINE";1;"RED";;;
13;"R4";"0603-NO";1;"10K";;;
14;"U1";"SOT23-5";1;"AP2112-3.3";;;
15;"X1";"WROOM32";1;"ESP32_WROOM32";;;
16;"U$12";"ADAFRUIT_TEXT_20MM";1;"";;;
17;"U$2";"HUZZAHLOGO";1;"";;;
18;"X2";"JSTPH2";1;"JSTPH";;;
19;"U$13";"PCBFEAT-REV-040";1;"";;;
